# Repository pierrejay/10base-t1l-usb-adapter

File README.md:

# Single Pair Ethernet 10BASE-T1L USB adapter

A USB ↔ SPE 10BASE-T1L adapter: plug it into any Linux host and get a
standard network interface that speaks Ethernet over a single twisted pair
(long-reach, up to ~1 km, 10 Mbit/s full-duplex). An easy way to give
a laptop, a Raspberry Pi, or an embedded SoC an SPE T1L port for bring-up and
diagnostics.

## Main components

| Part | Function | Datasheet |
|---|---|---|
| Microchip LAN9500A | USB 2.0 ↔ Ethernet MAC | [product page](https://www.microchip.com/en-us/product/lan9500a) |
| TI DP83TD510E | 10BASE-T1L PHY | [product page](https://www.ti.com/product/DP83TD510E) |

The LAN9500A runs in external PHY (MII) mode: its internal 100M PHY is
bypassed and the MII bus drives the DP83TD510E.

## Changelog - Rev 1

- Changed the SPE 24V TVS to a low-cap Ethernet part (`PESD2ETH-AX`) and moved it to
  the PHY side of the CMC for better DP83TD510E front-end protection.
- Updated the termination R/C parts to full 100 V-rated parts for better
  PoDL/cable-fault withstand margin.
- Reworked the cable-side routing, including a copper keepout under the cable
  area up to the CMC (NXP guidelines for UTP).
- Moved LINK LED control from the LAN9500A (unsupported in external PHY mode) to the DP83TD510E.
- Swapped PWR/LINK LED placement to simplify routing.
- Board size is now **51.5 × 22 mm** (Rev 0 was 50 × 22 mm).

## Enclosure

A 3D-printable case STEP model is provided for each of the hardware revisions. It needs a single ⌀2.5×8 mm flat head screw (Plastite or sheet metal/self-tapping screw) to attach the USB-side cap.

## Fabrication

Turnkey at JLCPCB. Import the EasyEDA Pro project, then order PCB + assembly in one shot. 

Rev 1 is also provided as a KiCad project in [`hw_rev1/kicad/`](hw_rev1/kicad/) (KiCad v9.0.7).

**4-layer PCB**: select the `JLC04161H-3313` stackup. The impedance-sensitive 
nets (USB-C D±, the MII bus, the T1L pair) are designed against that specific stackup.

## How it appears to Linux

Two chips, two drivers:

| Chip | Role | Linux driver | Notes |
|---|---|---|---|
| Microchip LAN9500A | USB 2.0 Ethernet MAC | `smsc95xx` | In mainline since forever, same family as the Raspberry Pi's own NIC. Works out of the box. |
| TI DP83TD510E | 10BASE-T1L PHY | `dp83td510` | In mainline since Linux 5.19, but **not always enabled** by distro kernels. Without it the link won't come up. |

When you plug the dongle in, `smsc95xx` enumerates and creates an interface
(`eth0`, `eth1`, … called `ethN` below). The MDIO scan finds the DP83TD510E
at address 0 (PHY ID `0x2000.0181`). **The PHY driver must be present**, or the
PHY falls back to *Generic PHY* and the T1L link never establishes.

> Quick identity check: `lsusb` should show VID `0424` / PID `9e00`.

## OS / driver support

| Host | `smsc95xx` (MAC) | `dp83td510` (PHY) | What to do |
|---|---|---|---|
| **Recent Ubuntu / Debian** (kernel ≥ 6.x) | usually built-in | usually built-in | Works out of the box when the PHY driver is enabled. Cable test (`ethtool --cable-test`) is kernel/driver-version dependent. |
| **Raspberry Pi OS** (Bookworm, ~6.x) | built-in | **absent** on the tested image | Build the PHY driver via DKMS (see below). Validated on Pi 3B+ / 6.12. |
| **Embedded target** (Buildroot / Yocto) | enable `CONFIG_USB_NET_SMSC95XX` | enable `CONFIG_DP83TD510_PHY` | Confirmed working from kernel **6.1 up** with the right driver/config in the BSP. Cable-test support is version-dependent, see the note below. |

> **Cable test on embedded kernels: it depends.** `ethtool --cable-test` needs a
> recent enough `dp83td510`. The 6.1-era driver may predate it, but the driver has
> been updated upstream since, so whether it's there comes down to exactly what
> your BSP ships (YMMV; check case by case). Where it's missing, the TDR/ALCD
> sequence can be driven directly over MDIO instead of through `ethtool`.

### Enabling the PHY driver as DKMS

On stock Raspberry Pi OS (and any host whose kernel doesn't ship `dp83td510`),
build it out-of-tree as a DKMS module so it survives reboots and kernel
updates. See the [`install-dp83td510-dkms.sh`](install-dp83td510-dkms.sh) script
(tested on RPi 3B+, very likely working on RPi 4, TBC for RPi 5).

After installing, unplug and replug the dongle, the PHY binds at USB
enumeration. Then `dmesg | grep -i DP83TD510` should read
`... attached PHY driver` (not `Generic PHY`).

## Quick start - Bring up a link

10BASE-T1L is point-to-point: one end is **master** (drives the clock), the other
**slave**. The DP83TD510E supports BASE-T1 auto-negotiation (IEEE 802.3cg) and
the dongle defaults to **preferred slave** so against a gateway, switch or media
converter that is master, the roles resolve automatically and the dongle will
not try to take master.

On a managed host (NetworkManager, `dhcpcd`, `systemd-networkd`, ...), the
interface may already be up and configured when the dongle is plugged in. Check
first, then bring it up manually only if it is still down:

```sh
ip link show ethN
sudo ip link set ethN up   # only if the interface is still DOWN / unmanaged
ethtool ethN               # Link detected: yes, Speed 10Mb/s, Duplex Full
sudo dhclient ethN         # only if DHCP was not already handled
```

A working link reads `10baseT1L/Full` and `Link detected: yes`.

You only need to force a role when auto-negotiation can't settle it: two
dongles back to back (both default to slave), or a peer running with AN disabled
/ a fixed role you have to match:

```sh
sudo ethtool -s ethN master-slave forced-master   # or forced-slave, to match the peer
```

## Throughput sanity check

Bench test: `iperf3` between a Mac and a Linux target, through this dongle and a
WAGO 852-1705 gateway. TCP throughput is stable in both directions at about line
rate:

- **downlink:** ~9.4 Mbit/s effective, with 0 retransmits in the captured run.
- **uplink:** ~9.4 Mbit/s effective.

For a 10 Mbit/s T1L link, that's the expected ceiling once Ethernet/IP/TCP
overhead is counted.

## Diagnostics with stock tools

`ethtool` and [`phytool`](https://github.com/wkz/phytool) cover the essentials —
no project-specific software needed. `ethtool` ships with every distro; `phytool`
often isn't packaged (e.g. on Raspberry Pi OS), but it builds in seconds:

```sh
git clone https://github.com/wkz/phytool && make -C phytool
sudo cp phytool/phytool /usr/local/bin/   # or anywhere on your PATH
```

### Link, speed, master/slave

```sh
ethtool ethN
#   Speed: 10Mb/s
#   Duplex: Full
#   Supported link modes:   10baseT1L/Full
#   master-slave cfg: forced master      (or preferred slave)
#   Link detected: yes
```

### Reliable link status (PHY_STS)

The Clause-22 BMSR link bit is latch-low on this PHY and gives timing false
negatives. The robust source is the vendor `PHY_STS` register (Clause 22, reg
`0x10`), bit 0 = link up:

```sh
phytool read ethN/0/0x10        # bit0 set => link up
```

### Signal quality (SQI / MSE)

The DP83TD510E reports a Mean-Square-Error metric (MMD VEND2 `0x1F`, reg
`0xA85`); lower MSE = cleaner signal = higher SQI (0–7). Native Clause-45 access
returns `EOPNOTSUPP` on the `smsc95xx` MDIO bus, so read it the way the kernel
does, **Clause-22-indirect** via the MMD access registers (`0x0D`/`0x0E`):

```sh
phytool write ethN/0/0x0d 0x001f   # MMD_CTRL: function=address, devad=0x1F
phytool write ethN/0/0x0e 0x0a85   # MMD_DATA: register = MSE_DETECT
phytool write ethN/0/0x0d 0x401f   # MMD_CTRL: function=data, devad=0x1F
phytool read  ethN/0/0x0e          # -> MSE, e.g. 0x001b
```

Reference (good link, on the bench): MSE `0x001b` → SQI 7/7, SNR ≈ 35 dB. The
SQI thresholds live in the `dp83td510` driver / TI datasheet.

### Cable test (TDR / ALCD)

On a kernel whose `dp83td510` includes cable test (≥ 6.x):

```sh
ethtool --cable-test ethN
```

- **Link up** → ALCD reports cable **length**.
- **Link down** → TDR reports a **fault** (open / short) and a location.

> ⚠ **Distance is not trustworthy out of the box.** The fault *type* (open vs
> short) is reliable; the *distance* is raw and the kernel's ×100 scaling looks
> wrong at short range (it reports ~25 m for a meter-ish-long cable). Real distance
> needs per-cable calibration (TI app note SNLA364).

The raw-graph form (`--cable-test-tdr`) is not supported by this driver.

## License

Licensed under `CERN-OHL-P-2.0` (cf. LICENSE file)

© Pierre Jay 2026

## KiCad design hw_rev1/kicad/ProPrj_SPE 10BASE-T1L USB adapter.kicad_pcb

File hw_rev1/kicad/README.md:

# KiCad

This KiCad project was imported from EasyEDA and is maintained with KiCad v9.0.7.

EasyEDA 3D model files are not versioned here. They should be regenerated locally with `easyeda2kicad` and the sync helper.

## Restore 3D Models

Requirements:

- `easyeda2kicad` installed and available in `PATH`
- local central library in `~/Documents/KiCad/easyeda2kicad`

From this directory:

```bash
EASYEDA_LIBRARY="$HOME/Documents/KiCad/easyeda2kicad"

./sync_easyeda_models.py . \
  --library "$EASYEDA_LIBRARY" \
  --pull-footprint-models
```

The script copies only the required models into `EASYEDA_MODELS/`, applies known 3D alignment fixes, and fetches missing parts through `easyeda2kicad` when possible.

## After 3D Alignment Fixes

If a model is manually realigned in KiCad, push the correction back to the local library:

```bash
EASYEDA_LIBRARY="$HOME/Documents/KiCad/easyeda2kicad"

./sync_easyeda_models.py . \
  --library "$EASYEDA_LIBRARY" \
  --push-to-library
```

Other projects can then reuse those fixes with `--pull-footprint-models`.

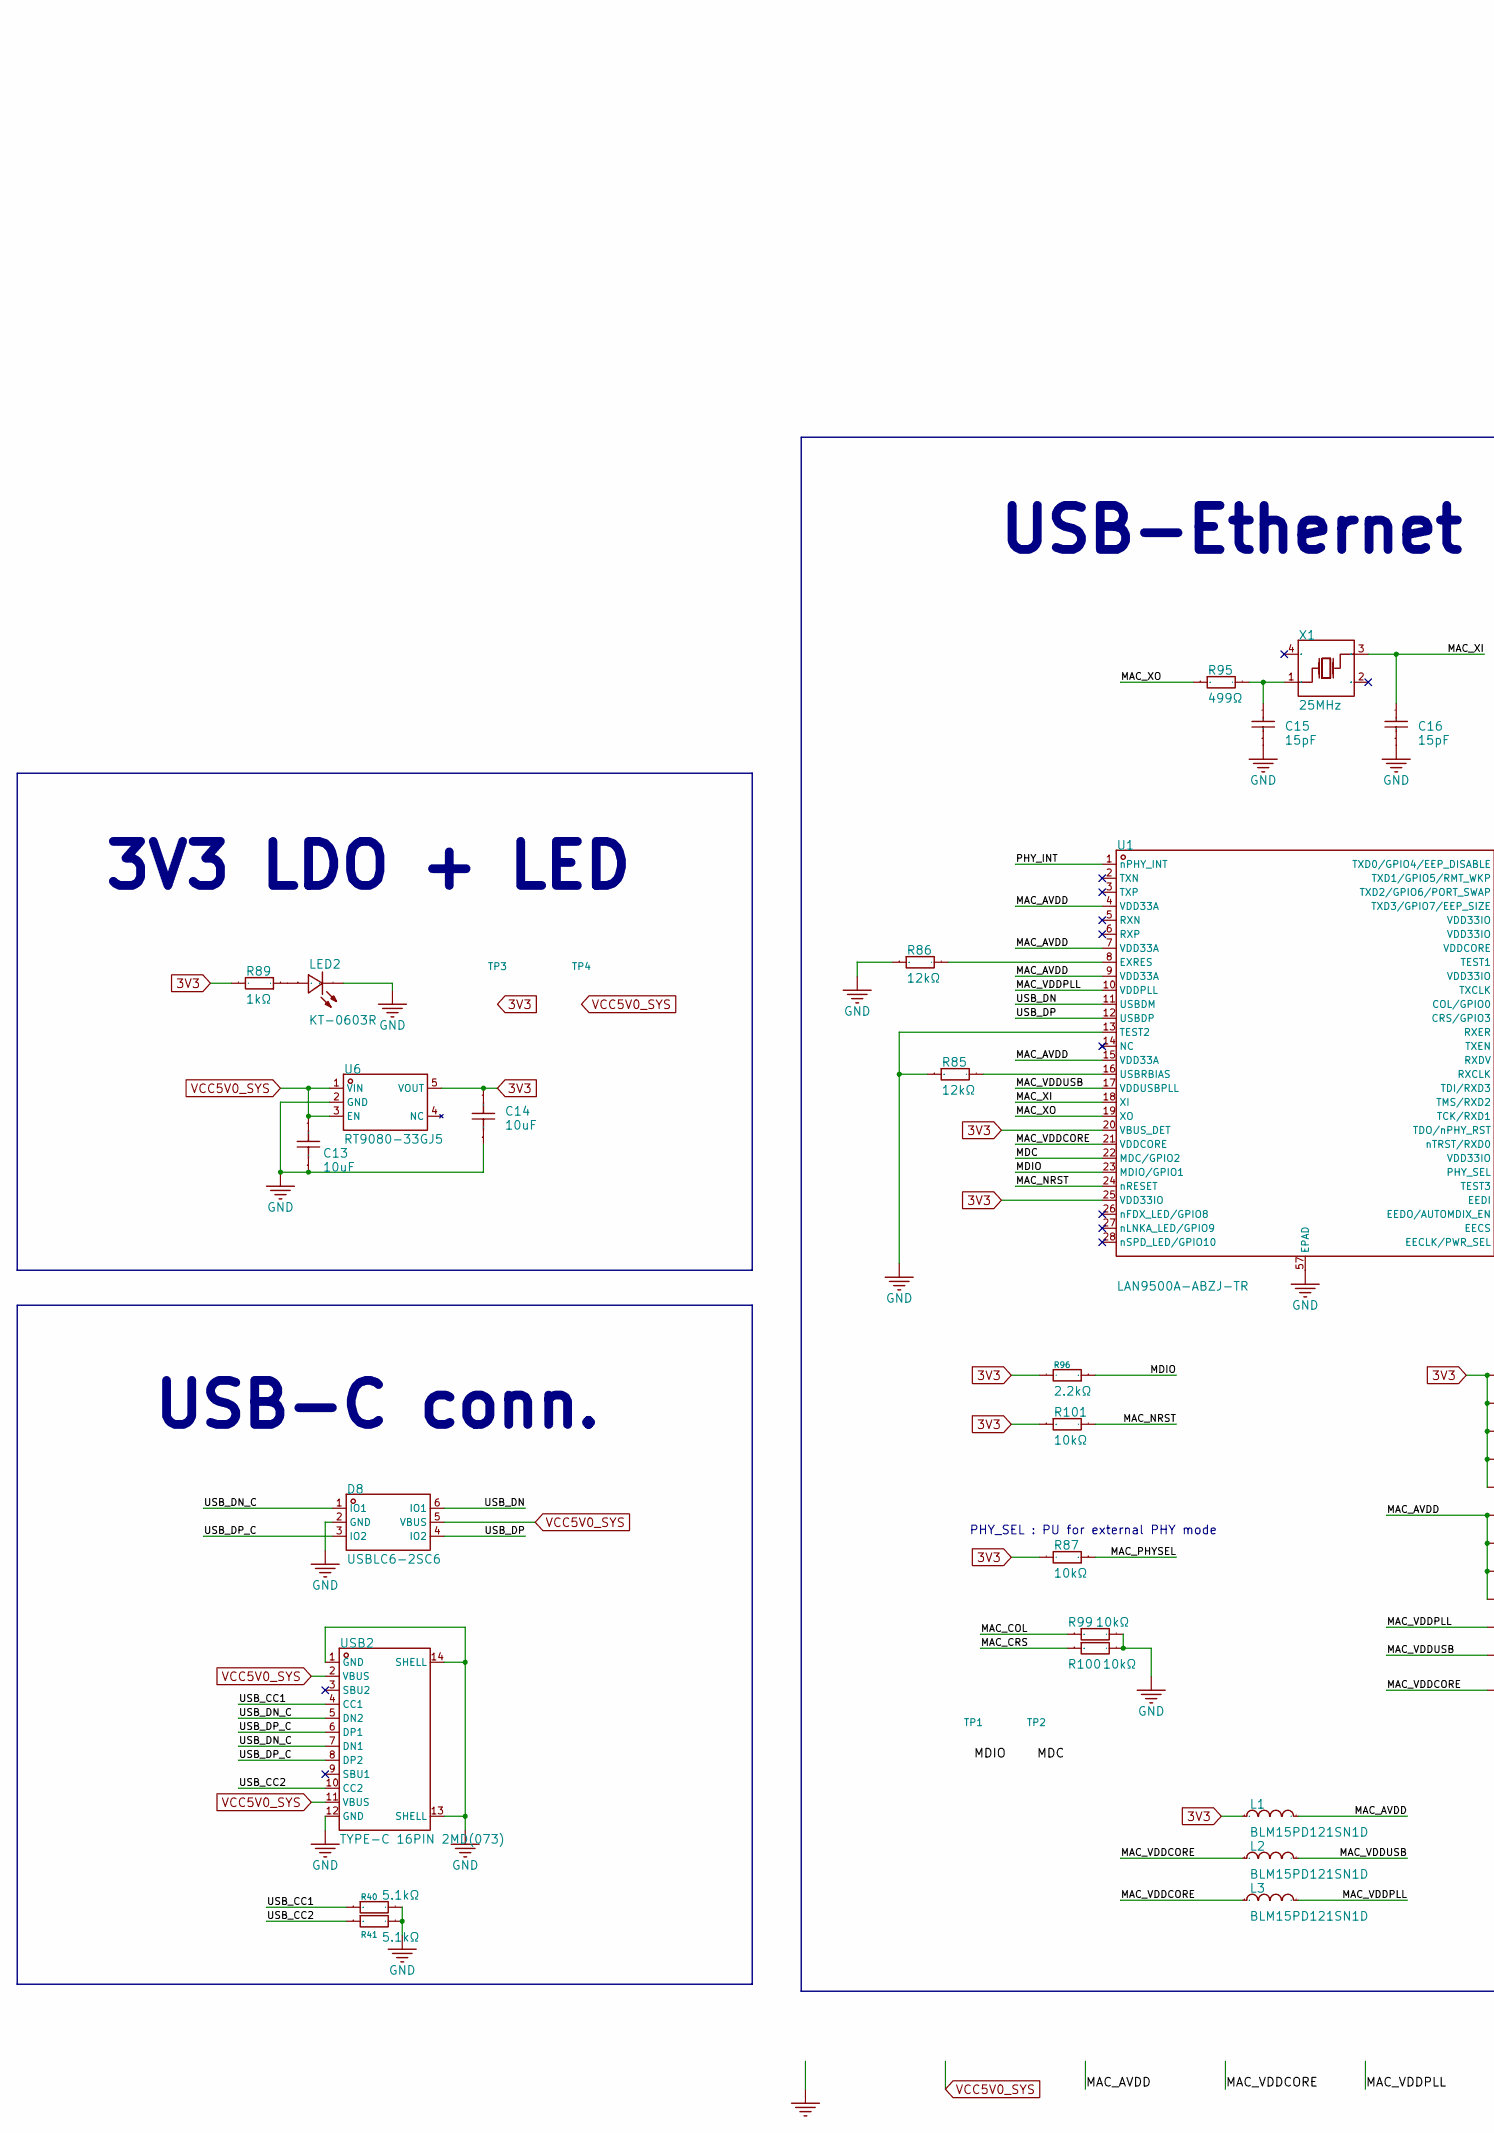
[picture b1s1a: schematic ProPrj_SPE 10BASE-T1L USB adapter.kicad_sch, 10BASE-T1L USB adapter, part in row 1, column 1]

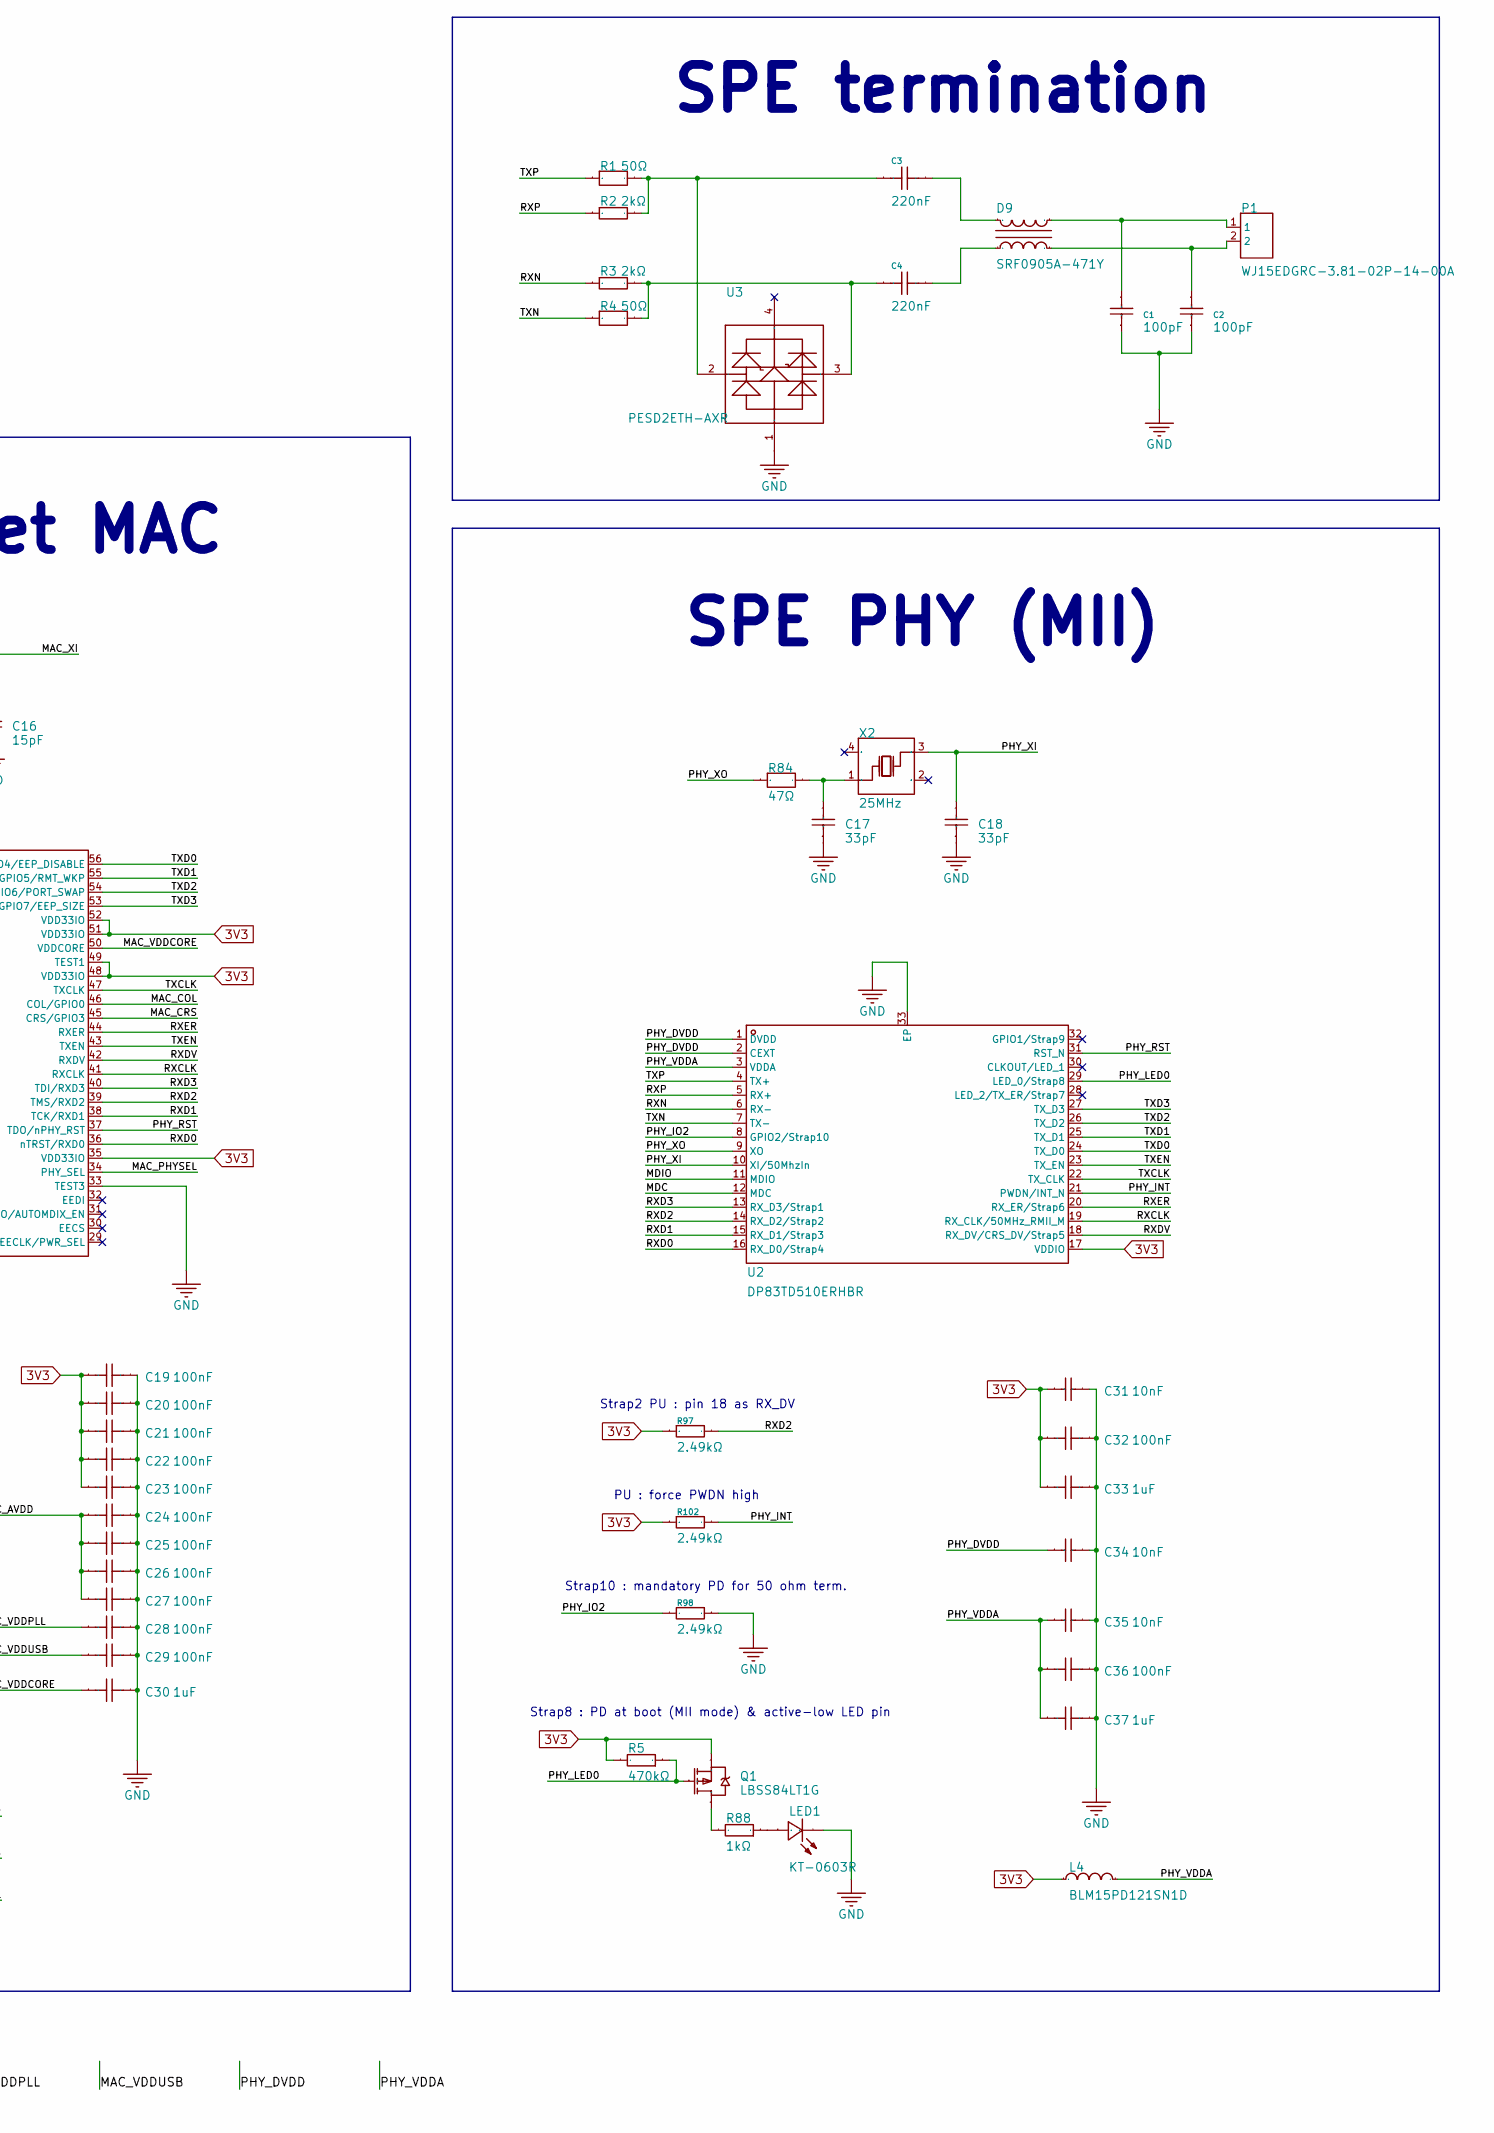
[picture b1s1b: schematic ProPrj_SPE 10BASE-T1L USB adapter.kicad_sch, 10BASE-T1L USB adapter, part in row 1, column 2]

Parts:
C1, C2: 100pF; C0603; Manufacturer Part CC0603JRNPO0BN101; LCSC Part Name 100pF ±5% 100V
C3, C4: 220nF; C0805; Manufacturer Part CC0805KKX7R0BB224; LCSC Part Name 220nF ±10% 100V
C13, C14: 10uF; C0603; Manufacturer Part CL10A106MQ8NNNC; LCSC Part Name 10uF ±20% 6.3V
C15, C16: 15pF; C0402; Manufacturer Part 0402CG150J500NT; LCSC Part Name 15pF ±5% 50V
C17, C18: 33pF; C0402; Manufacturer Part 0402CG330J500NT; LCSC Part Name 33pF ±5% 50V
C19, C20, C21, C22, C23, C24, C25, C26, C27, C28, C29, C32, C36: 100nF; C0402; Manufacturer Part CL05B104KO5NNNC; LCSC Part Name 100nF ±10% 16V
C30, C33, C37: 1uF; C0402; Manufacturer Part CL05A105KA5NQNC; LCSC Part Name 1uF ±10% 25V
C31, C34, C35: 10nF; C0402; Manufacturer Part CL05B103KB5NNNC; LCSC Part Name 10nF ±10% 50V
D8: USBLC6-2SC6; SOT-23-6_L2.9-W1.6-P0.95-LS2.8-BL; Manufacturer Part USBLC6-2SC6; LCSC Part Name ESD，可防30kV静电
D9: SRF0905A-471Y; FILTER-SMD_4P-L9.2-W6.0-TL-A; Manufacturer Part SRF0905A-471Y; LCSC Part Name 两路 共模滤波器 阻抗1000Ω@20MHz
L1, L2, L3, L4: BLM15PD121SN1D; L0402; Manufacturer Part BLM15PD121SN1D; LCSC Part Name 单路 0402磁珠 阻抗120Ω@100MHz
LED1, LED2: KT-0603R; LED-SMD_L1.6-W0.8-R-RD; Manufacturer Part KT-0603R; LCSC Part Name 0603 红灯 高亮
P1: WJ15EDGRC-3.81-02P-14-00A; CONN-TH_2P-P3.81_WJ15EDGRC-3.81-2P; Manufacturer Part WJ15EDGRC-3.81-02P-14-00A; LCSC Part Name 卡扣固定 1x2P 3.81mm 排数:1 每排P数:2
Q1: LBSS84LT1G; SOT-23_L2.9-W1.3-P1.90-LS2.4-BR; Manufacturer Part LBSS84LT1G; LCSC Part Name 1个P沟道 耐压:50V 电流:0.13A
R1, R4: 50Ω; R0603; Manufacturer Part RT0603BRE0750RL; LCSC Part Name 薄膜电阻 50Ω ±0.1% 100mW
R2, R3: 2kΩ; R0603; Manufacturer Part 0603WAF2001T5E; LCSC Part Name 2kΩ ±1% 100mW 厚膜电阻
R5: 470kΩ; R0402; Manufacturer Part 0402WGF4703TCE; LCSC Part Name 470kΩ ±1% 62.5mW 厚膜电阻
R40, R41: 5.1kΩ; R0402; Manufacturer Part 0402WGF5101TCE; LCSC Part Name 5.1kΩ ±1% 62.5mW 厚膜电阻
R84: 47Ω; R0402; Manufacturer Part FRC0402F47R0TS; LCSC Part Name 47Ω ±1% 62.5mW 厚膜电阻
R85, R86: 12kΩ; R0402; Manufacturer Part 0402WGF1202TCE; LCSC Part Name 12kΩ ±1% 62.5mW 厚膜电阻
R87, R99, R100, R101: 10kΩ; R0402; Manufacturer Part 0402WGF1002TCE; LCSC Part Name 10kΩ ±1% 62.5mW 厚膜电阻
R88, R89: 1kΩ; R0402; Manufacturer Part 0402WGF1001TCE; LCSC Part Name 1kΩ ±1% 62.5mW 厚膜电阻
R95: 499Ω; R0402; Manufacturer Part 0402WGF4990TCE; LCSC Part Name 499Ω ±1% 62.5mW 厚膜电阻
R96: 2.2kΩ; R0402; Manufacturer Part 0402WGF2201TCE; LCSC Part Name 2.2kΩ ±1% 62.5mW 厚膜电阻
R97, R98, R102: 2.49kΩ; R0402; Manufacturer Part 0402WGF2491TCE; LCSC Part Name 2.49kΩ ±1% 62.5mW 厚膜电阻
TP1: TestPoint; Pad_e105
TP2: TestPoint; Pad_e106
TP3: TestPoint; Pad_e107
TP4: TestPoint; Pad_e108
U1: LAN9500A-ABZJ-TR; QFN-56_L8.0-W8.0-P0.50-TL-EP6.1; Manufacturer Part LAN9500A-ABZJ-TR; LCSC Part Name LAN950x USB 2.0 到 10/100 以太网控制器
U2: DP83TD510ERHBR; HVQFN-32_L5.0-W5.0-P0.50-TL-EP2.1; Manufacturer Part DP83TD510ERHBR; LCSC Part Name Ultra Low Power 802.3cg 10Base-T1L 10M 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
U3: PESD2ETH-AXR; SOT-143_L2.9-W1.3-P1.92-LS2.3-BL; Manufacturer Part PESD2ETH-AXR; LCSC Part Name ESD 5V截止 峰值浪涌电流：4A@8/20us
U6: RT9080-33GJ5; TSOT-23-5_L2.9-W1.6-P0.95-LS2.8-BL; Manufacturer Part RT9080-33GJ5; LCSC Part Name 静态电流2μA，输出电流600mA的低压差线性稳压器
USB2: TYPE-C 16PIN 2MD(073); USB-C-SMD_TYPE-C-6PIN-2MD-073; Manufacturer Part TYPE-C 16PIN 2MD(073); LCSC Part Name Type-C 母 卧贴
X1: 25MHz; CRYSTAL-SMD_4P-L3.2-W2.5-BL; Manufacturer Part X322525MOB4SI; LCSC Part Name YSX321SL 25MHZ 4P 3225 12PF ±10PPM -40~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
X2: 25MHz; CRYSTAL-SMD_4P-L3.2-W2.5-BL-2; Manufacturer Part X322525MSB4SI; LCSC Part Name YSX321SL 25MHZ 4P 3225 20PF ±10PPM -40~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

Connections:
3V3: C14.2, C19.1, C20.1, C21.1, C22.1, C23.1, C31.1, C32.1, C33.1, L1.1, L4.1, Q1.2 (S), R5.2, R87.2, R89.2, R96.2, R97.1, R101.1, R102.1, TP3.1 (1_1), U1.20 (VBUS_DET), U1.25 (VDD33IO), U1.35 (VDD33IO), U1.48 (VDD33IO), U1.49 (TEST1), U1.51 (VDD33IO), U1.52 (VDD33IO), U2.17 (VDDIO), U6.5 (VOUT)
/MAC_AVDD: C24.1, C25.1, C26.1, C27.1, L1.2, U1.4 (VDD33A), U1.7 (VDD33A), U1.9 (VDD33A), U1.15 (VDD33A)
/MAC_COL: R99.1, U1.46 (COL/GPIO0)
/MAC_CRS: R100.1, U1.45 (CRS/GPIO3)
/MAC_NRST: R101.2, U1.24 (nRESET)
/MAC_PHYSEL: R87.1, U1.34 (PHY_SEL)
/MAC_VDDCORE: C30.1, L2.1, L3.1, U1.21 (VDDCORE), U1.50 (VDDCORE)
/MAC_VDDPLL: C28.1, L3.2, U1.10 (VDDPLL)
/MAC_VDDUSB: C29.1, L2.2, U1.17 (VDDUSBPLL)
/MAC_XI: C16.2, U1.18 (XI), X1.3 (OSC2)
/MAC_XO: R95.1, U1.19 (XO)
/MDC: TP2.1 (1_1), U1.22 (MDC/GPIO2), U2.12 (MDC)
/MDIO: R96.1, TP1.1 (1_1), U1.23 (MDIO/GPIO1), U2.11 (MDIO)
/PHY_DVDD: C34.1, U2.1 (DVDD), U2.2 (CEXT)
/PHY_INT: R102.2, U1.1 (nPHY_INT), U2.21 (PWDN/INT_N)
/PHY_IO2: R98.2, U2.8 (GPIO2/Strap10)
/PHY_LED0: Q1.1 (G), R5.1, U2.29 (LED_0/Strap8)
/PHY_RST: U1.37 (TDO/nPHY_RST), U2.31 (RST_N)
/PHY_VDDA: C35.1, C36.1, C37.1, L4.2, U2.3 (VDDA)
/PHY_XI: C18.2, U2.10 (XI/50MhzIn), X2.3 (OSC2)
/PHY_XO: R84.1, U2.9 (XO)
/RXCLK: U1.41 (RXCLK), U2.19 (RX_CLK/50MHz_RMII_M)
/RXD0: U1.36 (nTRST/RXD0), U2.16 (RX_D0/Strap4)
/RXD1: U1.38 (TCK/RXD1), U2.15 (RX_D1/Strap3)
/RXD2: R97.2, U1.39 (TMS/RXD2), U2.14 (RX_D2/Strap2)
/RXD3: U1.40 (TDI/RXD3), U2.13 (RX_D3/Strap1)
/RXDV: U1.42 (RXDV), U2.18 (RX_DV/CRS_DV/Strap5)
/RXER: U1.44 (RXER), U2.20 (RX_ER/Strap6)
/RXN: R3.1, U2.6 (RX-)
/RXP: R2.1, U2.5 (RX+)
/TXCLK: U1.47 (TXCLK), U2.22 (TX_CLK)
/TXD0: U1.56 (TXD0/GPIO4/EEP_DISABLE), U2.24 (TX_D0)
/TXD1: U1.55 (TXD1/GPIO5/RMT_WKP), U2.25 (TX_D1)
/TXD2: U1.54 (TXD2/GPIO6/PORT_SWAP), U2.26 (TX_D2)
/TXD3: U1.53 (TXD3/GPIO7/EEP_SIZE), U2.27 (TX_D3)
/TXEN: U1.43 (TXEN), U2.23 (TX_EN)
/TXN: R4.1, U2.7 (TX-)
/TXP: R1.1, U2.4 (TX+)
/USB_CC1: R40.1, USB2.4 (CC1)
/USB_CC2: R41.1, USB2.10 (CC2)
/USB_DN: D8.6 (IO1), U1.11 (USBDM)
/USB_DN_C: D8.1 (IO1), USB2.5 (DN2), USB2.7 (DN1)
/USB_DP: D8.4 (IO2), U1.12 (USBDP)
/USB_DP_C: D8.3 (IO2), USB2.6 (DP1), USB2.8 (DP2)
GND: C1.1, C2.1, C13.1, C14.1, C15.1, C16.1, C17.1, C18.1, C19.2, C20.2, C21.2, C22.2, C23.2, C24.2, C25.2, C26.2, C27.2, C28.2, C29.2, C30.2, C31.2, C32.2, C33.2, C34.2, C35.2, C36.2, C37.2, D8.2 (GND), LED1.2 (K), LED2.2 (K), R40.2, R41.2, R85.1, R86.1, R98.1, R99.2, R100.2, U1.13 (TEST2), U1.33 (TEST3), U1.57 (EPAD), U2.33 (EP), U3.1, U6.2 (GND), USB2.1 (GND), USB2.12 (GND), USB2.13 (SHELL), USB2.14 (SHELL)
unnamed: C1.2, D9.4, P1.1
unnamed: C2.2, D9.3, P1.2
unnamed: C3.1, R1.2, R2.2, U3.2
unnamed: C3.2, D9.1
unnamed: C4.1, R3.2, R4.2, U3.3
unnamed: C4.2, D9.2
unnamed: LED1.1 (A), R88.1
unnamed: LED2.1 (A), R89.1
unnamed: Q1.3 (D), R88.2
unnamed: R86.2, U1.8 (EXRES)
unnamed: R85.2, U1.16 (USBRBIAS)
unnamed: C15.2, R95.2, X1.1 (OSC1)
unnamed: C17.2, R84.2, X2.1 (OSC1)
VCC5V0_SYS: C13.2, D8.5 (VBUS), TP4.1 (1_1), U6.1 (VIN), U6.3 (EN), USB2.2 (VBUS), USB2.11 (VBUS)

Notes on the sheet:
SPE PHY (MII)
PHY_SEL : PU for external PHY mode
Strap10 : mandatory PD for 50 ohm term.
Strap8 : PD at boot (MII mode) & active-low LED pin
3V3 LDO + LED
USB-Ethernet MAC
PU : force PWDN high
SPE termination
Strap2 PU : pin 18 as RX_DV
USB-C conn.

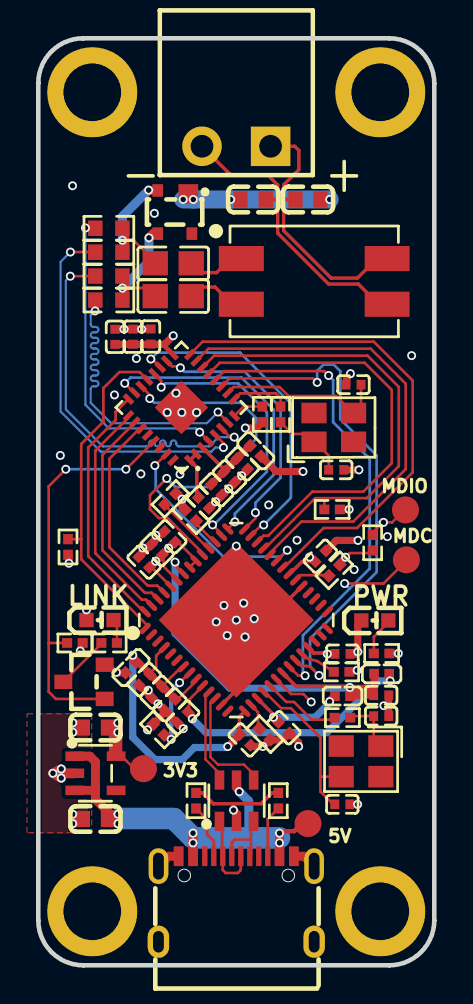
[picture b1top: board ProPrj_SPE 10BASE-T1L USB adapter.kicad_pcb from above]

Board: 4 copper layers, 22.0 x 51.5 mm, 71 parts (0 on the bottom side), 59 nets.

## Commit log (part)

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2026-06-06 Update rev1 schematic to remove screenshots from vendor datasheets
2026-06-07 Fix LINK LED PMOS
2026-06-07 Clean up schematic drawing
2026-06-29 Add KiCad files
